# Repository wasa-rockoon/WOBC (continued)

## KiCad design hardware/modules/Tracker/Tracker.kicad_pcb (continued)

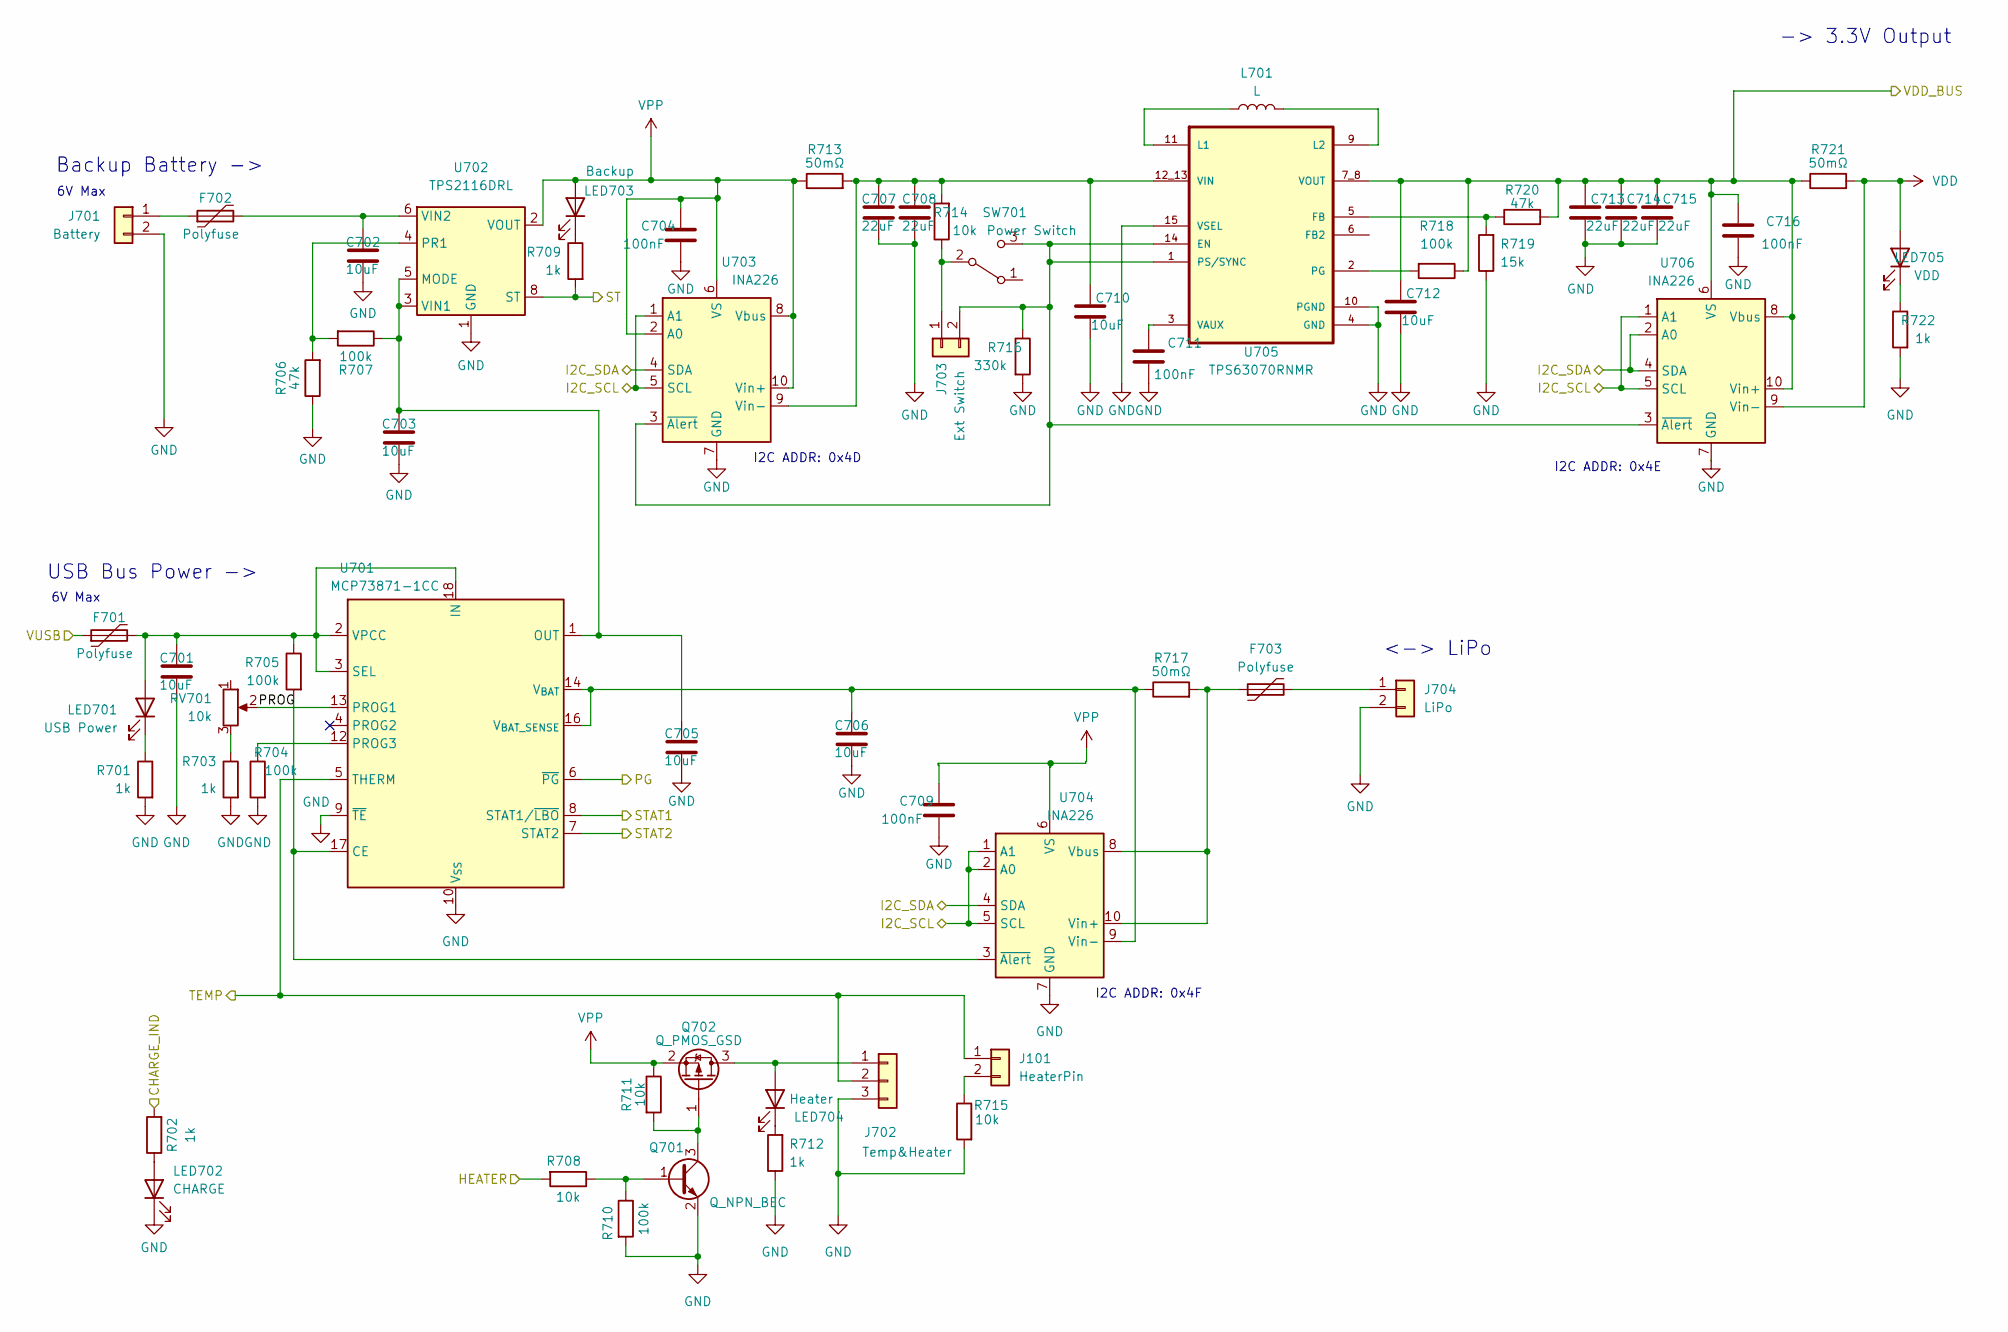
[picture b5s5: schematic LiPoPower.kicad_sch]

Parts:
C701, C702, C703, C705, C706, C710, C712: 10uF; C_0603_1608Metric; LCSC C96446
C704, C709, C711, C716: 100nF; C_0402_1005Metric; LCSC C1525
C707, C708, C713, C714, C715: 22uF; C_0805_2012Metric; LCSC C45783
F701, F702, F703: Polyfuse; Fuse_1206_3216Metric; LCSC C883133
J101: HeaterPin; PinHeader_1x02_P1.27mm_Vertical
J701: Battery; JST_XH_B2B-XH-A_1x02_P2.50mm_Vertical
J702: Temp&Heater; JST_PH_B3B-PH-K_1x03_P2.00mm_Vertical
J703: Ext Switch; JST_PH_B2B-PH-K_1x02_P2.00mm_Vertical
J704: LiPo; JST_PH_B2B-PH-K_1x02_P2.00mm_Vertical
L701: L; L_Wuerth_WE-TPC-3816; LCSC C3033018
LED701: USB Power; LED_0805_2012Metric; LCSC C2297
LED702: CHARGE; LED_0805_2012Metric; LCSC C2296
LED703: Backup; LED_0805_2012Metric; LCSC C2296
LED704: Heater; LED_0805_2012Metric; LCSC C2296
LED705: VDD; LED_0805_2012Metric; LCSC C2297
Q701: Q_NPN_BEC; SOT-23; LCSC C20526
Q702: Q_PMOS_GSD; SOT-23; LCSC C15127
R701, R702, R703, R709, R712, R722: 1k; R_0402_1005Metric; LCSC C11702
R704, R705, R707, R710, R718: 100k; R_0402_1005Metric; LCSC C25741
R706, R720: 47k; R_0402_1005Metric; LCSC C25792
R708, R711, R714, R715: 10k; R_0402_1005Metric; LCSC C25744
R713, R717, R721: 50mΩ; R_0805_2012Metric; LCSC C247602
R716: 330k; R_0402_1005Metric; LCSC C23137
R719: 15k; R_0402_1005Metric; LCSC C25756
RV701: 10k; Potentiometer_Bourns_TC33X_Vertical; LCSC C719176
SW701: Power Switch; SW_Slide_SPDT_Straight_CK_OS102011MS2Q
U701: MCP73871-1CC; QFN-20-1EP_4x4mm_P0.5mm_EP2.5x2.5mm; LCSC C511310
U702: TPS2116DRL; SOT-583-8; LCSC C3235557
U703, U704, U706: INA226; VSSOP-10_3x3mm_P0.5mm; LCSC C49851
U705: TPS63070RNMR; VREG_TPS63070RNMR; LCSC C109322

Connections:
/ESP32/CAN_RX: U701.7 (STAT2); also elsewhere on the board
/ESP32/CAN_TX: U701.8 (STAT1/~LBO); also elsewhere on the board
/ESP32/GPIO6/ADC1_CH5: R709.2, U702.8 (ST); also elsewhere on the board
/ESP32/GPIO7/ADC1_CH6: J101.1, J702.2, U701.5 (THERM); also elsewhere on the board
/ESP32/GPIO8/ADC1_CH7: R702.2; also elsewhere on the board
/ESP32/GPIO9/ADC1_CH8: R708.2; also elsewhere on the board
/ESP32/GPIO10/ADC1_CH9: U701.6 (~PG); also elsewhere on the board
/ESP32/I2C_SCL: U703.1 (A1), U703.5 (SCL), U704.1 (A1), U704.2 (A0), U704.5 (SCL), U706.1 (A1), U706.5 (SCL); also elsewhere on the board
/ESP32/I2C_SDA: U703.4 (SDA), U704.4 (SDA), U706.2 (A0), U706.4 (SDA); also elsewhere on the board
/ESP32/VUSB: F701.1; also elsewhere on the board
/Lipo/PROG: RV701.2, U701.13 (PROG1)
GND: C701.2, C702.2, C703.2, C704.2, C705.2, C706.2, C707.2, C708.2, C709.2, C710.2, C711.2, C712.2, C713.2, C714.2, C715.2, C716.2, J701.2, J702.3, J704.2, LED702.1 (K), Q701.2 (E), R701.2, R703.2, R704.2, R706.1, R710.2, R712.1, R715.2, R716.2, R719.1, R722.2, U701.9 (~TE), U701.10 (V_{SS}), U701.11 (V_{SS}), U701.21 (V_{SS}), U702.1 (GND), U703.7 (GND), U704.7 (GND), U705.4 (GND), U705.10 (PGND), U705.15 (VSEL), U706.7 (GND); also elsewhere on the board
unnamed: J101.2, R715.1
unnamed: F702.1, J701.1
unnamed: J702.1, LED704.2 (A), Q702.3 (D)
unnamed: J703.1, R714.1, SW701.2 (B)
unnamed: J703.2, R716.1, SW701.3 (C), U703.3 (~Alert), U705.1 (PS/SYNC), U705.14 (EN), U706.3 (~Alert)
unnamed: F703.2, J704.1
unnamed: C701.1, F701.2, LED701.2 (A), R705.1, U701.2 (VPCC), U701.3 (SEL), U701.18 (IN), U701.19 (IN)
unnamed: LED701.1 (K), R701.1
unnamed: LED702.2 (A), R702.1
unnamed: LED703.1 (K), R709.1
unnamed: LED704.1 (K), R712.2
unnamed: LED705.1 (K), R722.1
unnamed: Q701.1 (B), R708.1, R710.1
unnamed: Q701.3 (C), Q702.1 (G), R711.2
unnamed: R703.1, RV701.3
unnamed: R705.2, U701.17 (CE), U704.3 (~Alert)
unnamed: R704.1, U701.12 (PROG3)
unnamed: C706.1, R717.1, U701.14 (V_{BAT}), U701.15 (V_{BAT}), U701.16 (V_{BAT_SENSE}), U704.9 (Vin-)
unnamed: C703.1, C705.1, R707.1, U701.1 (OUT), U701.20 (OUT), U702.3 (VIN1), U702.5 (MODE)
unnamed: R706.2, R707.2, U702.4 (PR1)
unnamed: C702.1, F702.2, U702.6 (VIN2)
unnamed: C707.1, C708.1, C710.1, R713.2, R714.2, U703.9 (Vin-), U705.12_13 (VIN)
unnamed: F703.1, R717.2, U704.8 (Vbus), U704.10 (Vin+)
unnamed: R719.2, R720.1, U705.5 (FB)
unnamed: L701.1, U705.11 (L1)
unnamed: L701.2, U705.9 (L2)
unnamed: R718.2, U705.2 (PG)
unnamed: C711.1, U705.3 (VAUX)
VDD: C712.1, C713.1, C714.1, C715.1, C716.1, LED705.2 (A), R718.1, R720.2, R721.1, R721.2, U705.7_8 (VOUT), U706.6 (VS), U706.8 (Vbus), U706.9 (Vin-), U706.10 (Vin+); also elsewhere on the board
VPP: C704.1, C709.1, LED703.2 (A), Q702.2 (S), R711.1, R713.1, U702.2 (VOUT), U702.7 (VOUT), U703.2 (A0), U703.6 (VS), U703.8 (Vbus), U703.10 (Vin+), U704.6 (VS)

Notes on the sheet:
6V Max
USB Bus Power ->
<-> LiPo
I2C ADDR: 0x4D
I2C ADDR: 0x4F
-> 3.3V Output
I2C ADDR: 0x4E
Backup Battery ->

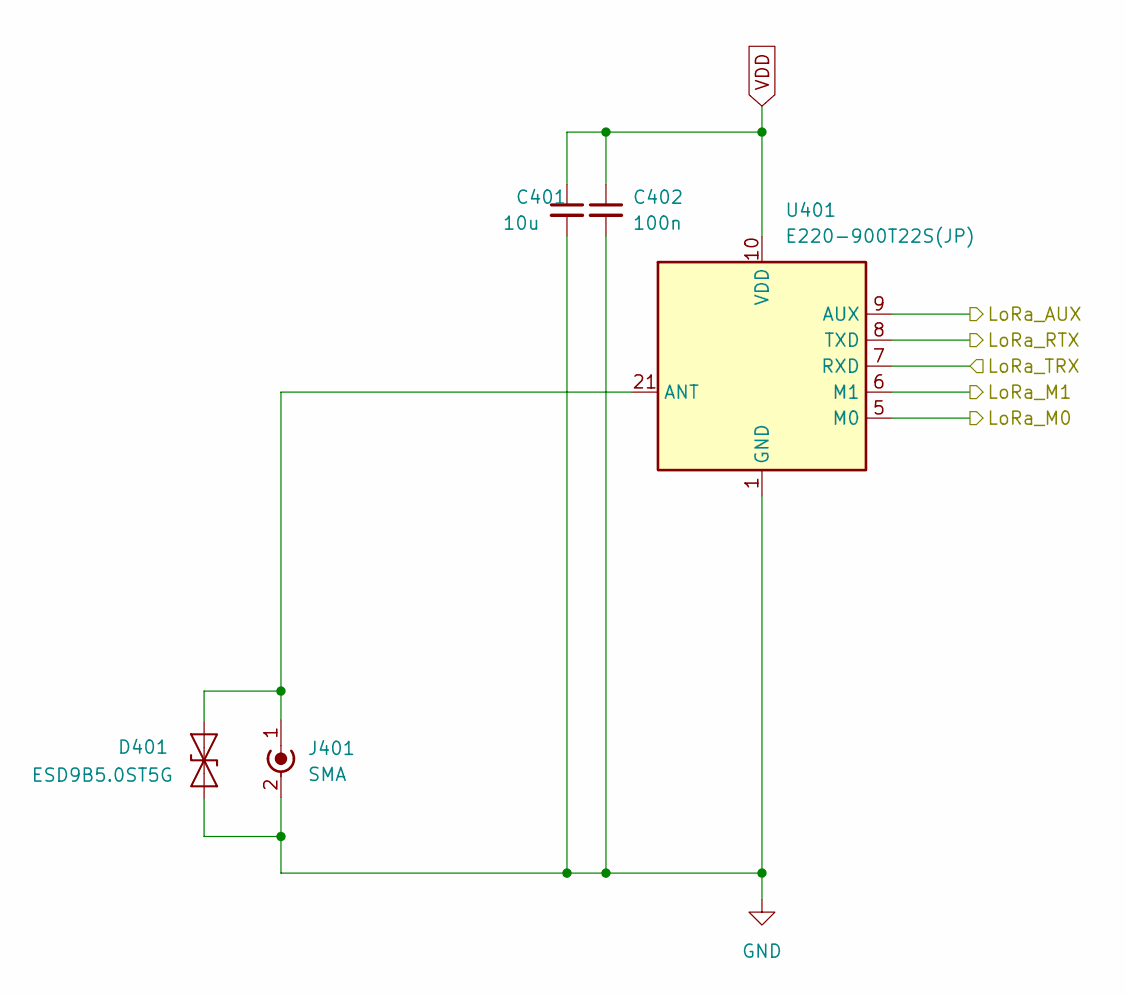
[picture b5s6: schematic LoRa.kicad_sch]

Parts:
C401: 10u; C_0603_1608Metric; LCSC C96446
C402: 100n; C_0402_1005Metric; LCSC C1525
D401: ESD9B5.0ST5G; D_SOD-882D; LCSC C7420372
J401: SMA; SMA_Amphenol_132203-12_Horizontal; LCSC C2693813
U401: E220-900T22S(JP)

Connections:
/ESP32/GPIO11: U401.6 (M1); also elsewhere on the board
/ESP32/GPIO12: U401.5 (M0); also elsewhere on the board
/ESP32/GPIO38: U401.7 (RXD); also elsewhere on the board
/ESP32/GPIO39: U401.8 (TXD); also elsewhere on the board
/ESP32/GPIO40: U401.9 (AUX); also elsewhere on the board
GND: C401.2, C402.2, D401.1 (A1), J401.2 (Ext), U401.1 (GND), U401.2 (GND), U401.3 (GND), U401.4 (GND), U401.11 (GND), U401.13 (GND), U401.19 (GND), U401.20 (GND), U401.22 (GND); also elsewhere on the board
unnamed: D401.2 (A2), J401.1 (In), U401.21 (ANT)
VDD: C401.1, C402.1, U401.10 (VDD); also elsewhere on the board

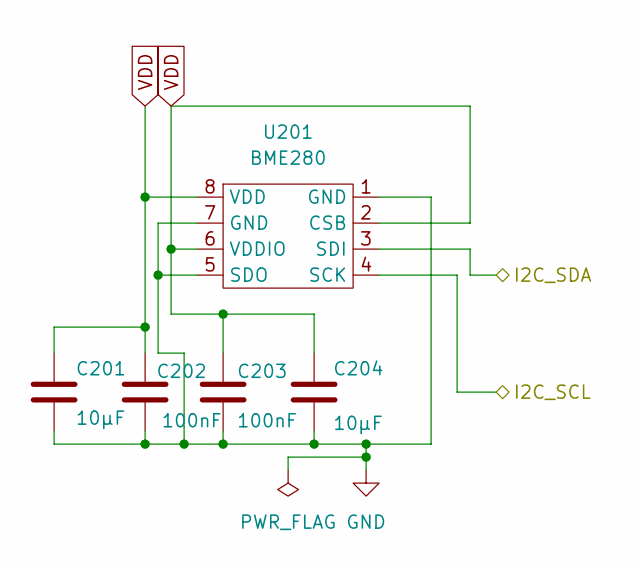
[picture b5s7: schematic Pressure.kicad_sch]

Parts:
C201, C204: 10μF; C_0603_1608Metric; LCSC C96446
C202, C203: 100nF; C_0402_1005Metric; LCSC C1525
U201: BME280; LCSC C92489

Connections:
/ESP32/I2C_SCL: U201.4 (SCK); also elsewhere on the board
/ESP32/I2C_SDA: U201.3 (SDI); also elsewhere on the board
GND: C201.2, C202.2, C203.2, C204.2, U201.1 (GND), U201.5 (SDO), U201.7 (GND); also elsewhere on the board
VDD: C201.1, C202.1, C203.1, C204.1, U201.2 (CSB), U201.6 (VDDIO), U201.8 (VDD); also elsewhere on the board

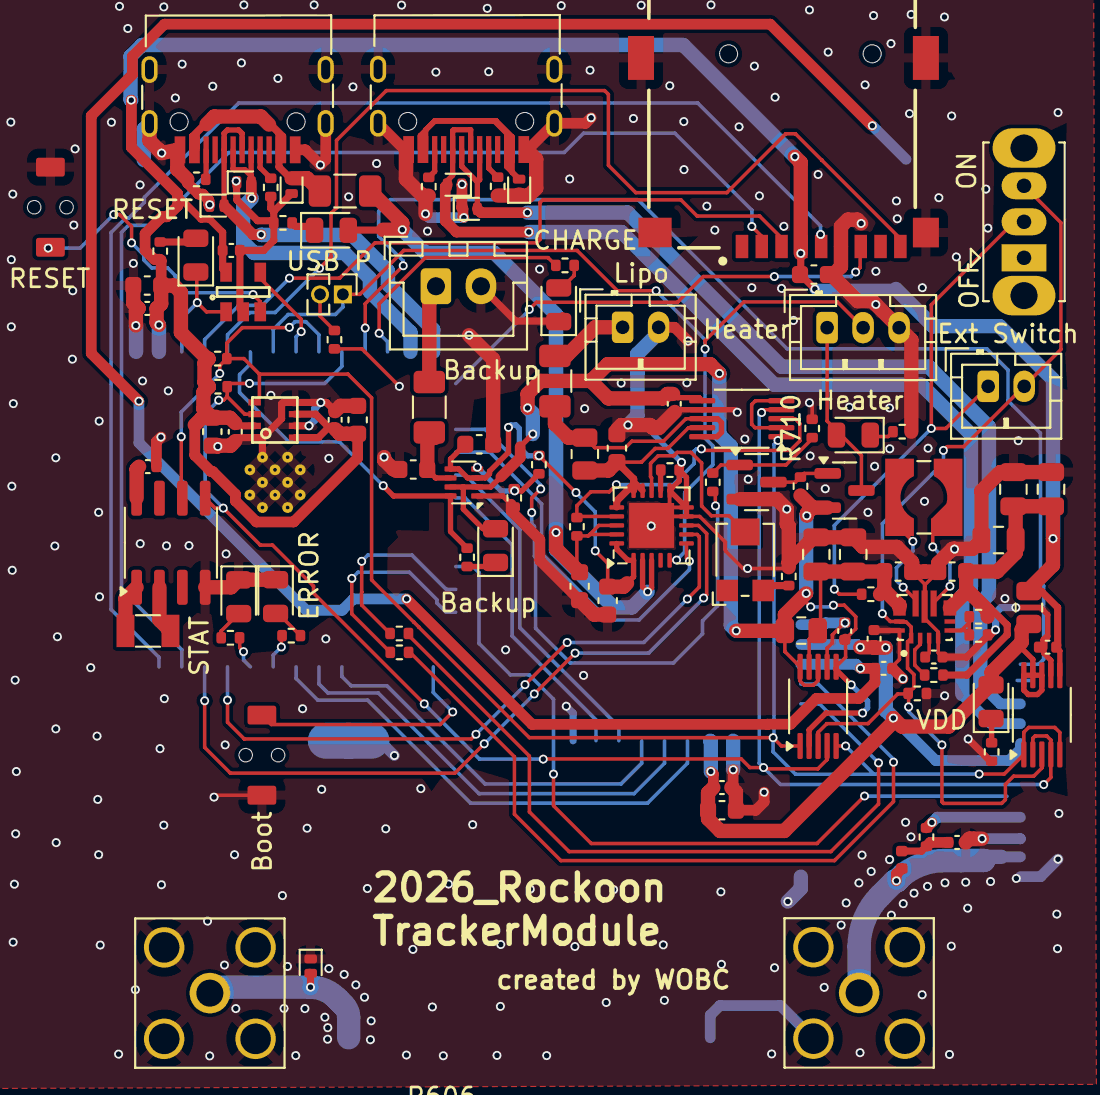
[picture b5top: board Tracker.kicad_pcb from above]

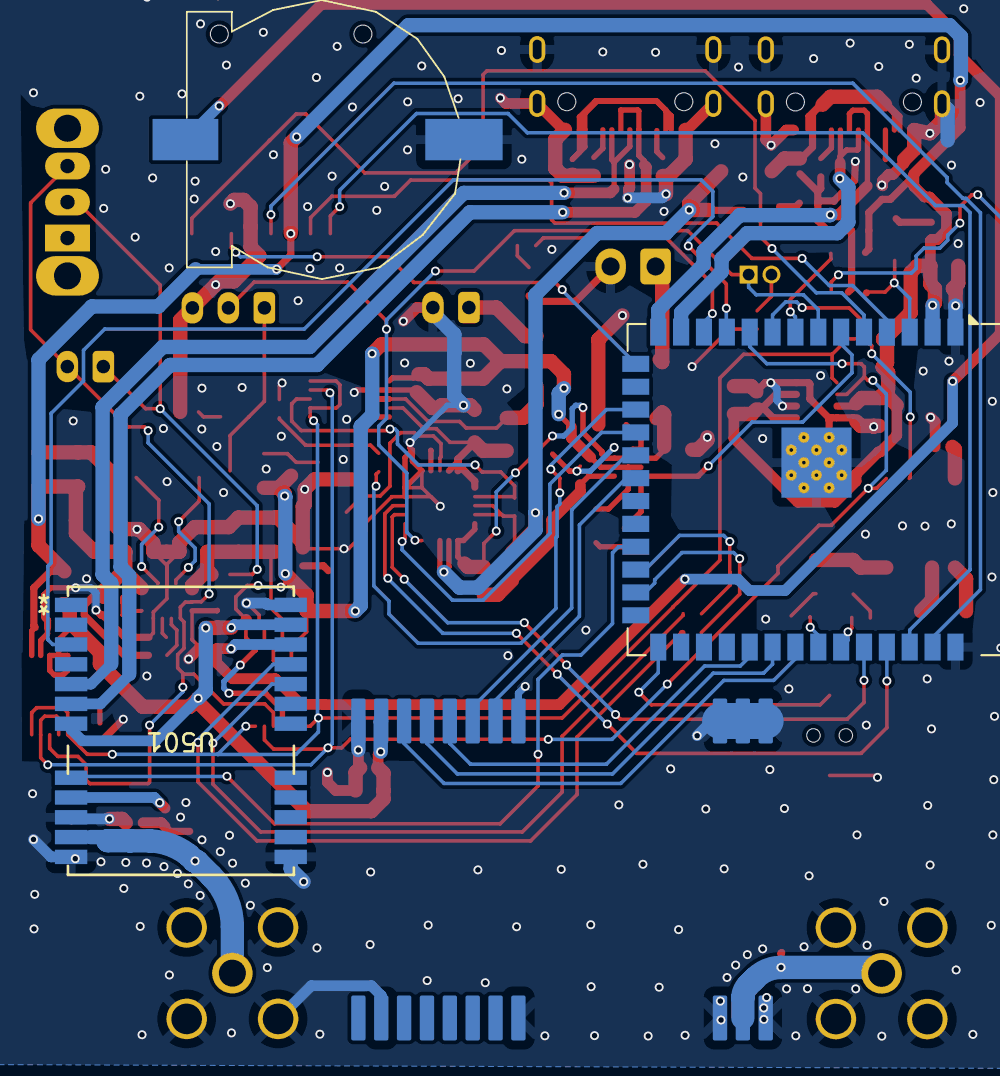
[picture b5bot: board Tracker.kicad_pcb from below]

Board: 2 copper layers, 114 parts (4 on the bottom side), 84 nets.

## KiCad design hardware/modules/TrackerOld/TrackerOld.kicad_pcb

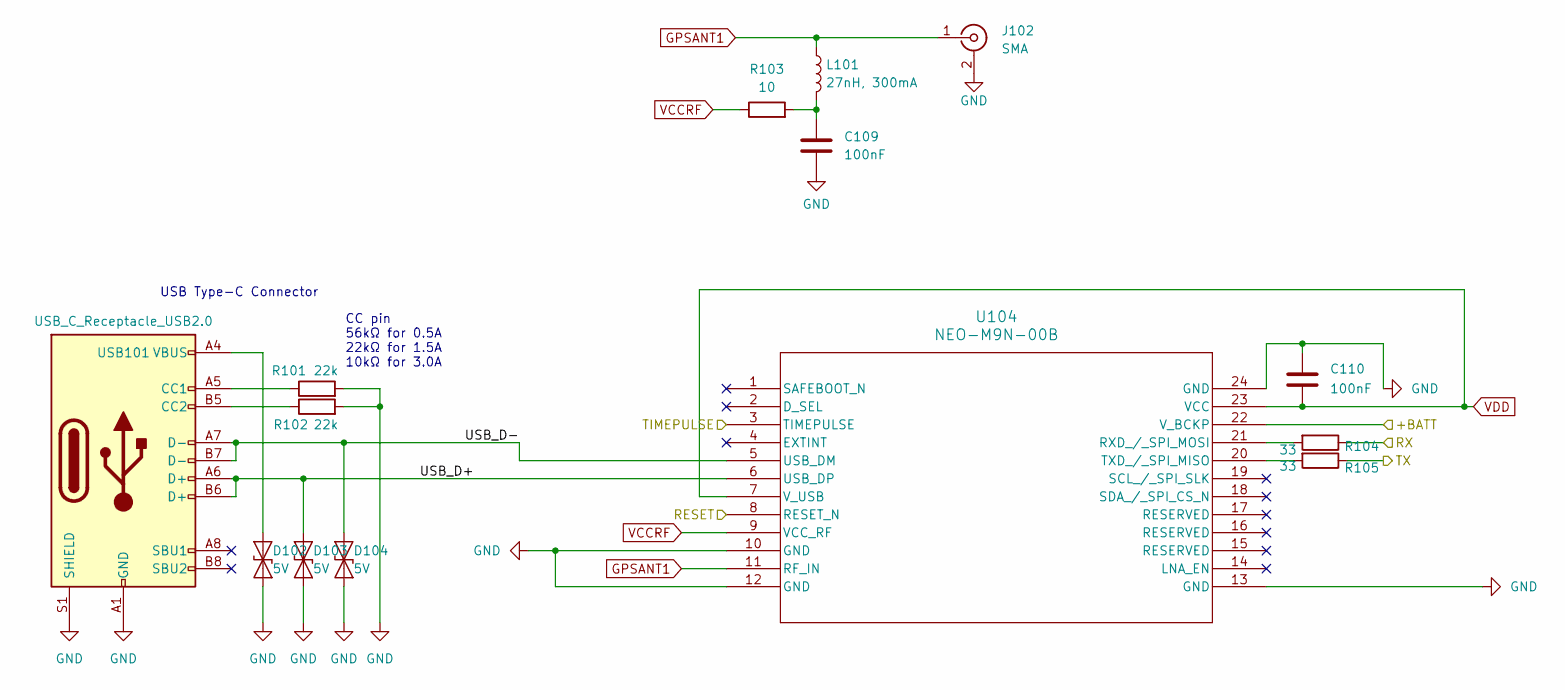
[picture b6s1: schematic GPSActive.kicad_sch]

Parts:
C109, C110: 100nF; C_0402_1005Metric; LCSC C1525
D102, D103, D104: 5V; D_SOD-882D; LCSC C7420372
J102: SMA; SMA_Amphenol_132203-12_Horizontal; LCSC C2693813
L101: 27nH, 300mA; L_0402_1005Metric
R101, R102: 22k; R_0402_1005Metric; LCSC C25768
R103: 10; R_0402_1005Metric; LCSC C25139
R104, R105: 33; R_0402_1005Metric; LCSC C25105
U104: NEO-M9N-00B; SMT_9N-00B_UBL
USB101: USB_C_Receptacle_USB2.0; USB_C_TYPEC-301S-ACP16X7; LCSC C2982481

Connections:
/ESP32/GPIO18: U104.3 (TIMEPULSE); also elsewhere on the board
/ESP32/GPIO21: U104.8 (RESET_N); also elsewhere on the board
/ESP32/GPIO47: R105.1; also elsewhere on the board
/ESP32/GPIO48: R104.1; also elsewhere on the board
/GPSActive/+BATT: U104.22 (V_BCKP)
/GPSActive/USB_D+: D103.2 (A2), U104.6 (USB_DP), USB101.A6 (D+), USB101.B6 (D+)
/GPSActive/USB_D-: D104.2 (A2), U104.5 (USB_DM), USB101.A7 (D-), USB101.B7 (D-)
GND: C109.2, C110.1, D102.1 (A1), D103.1 (A1), D104.1 (A1), J102.2 (Ext), R101.2, R102.2, U104.10 (GND), U104.12 (GND), U104.13 (GND), U104.24 (GND), USB101.A1 (GND), USB101.A12 (GND), USB101.B1 (GND), USB101.B12 (GND), USB101.S1 (SHIELD); also elsewhere on the board
GPSANT1: J102.1 (In), L101.1, U104.11 (RF_IN)
unnamed: C109.1, L101.2, R103.2
unnamed: D102.2 (A2), USB101.A4 (VBUS), USB101.A9 (VBUS), USB101.B4 (VBUS), USB101.B9 (VBUS)
unnamed: R104.2, U104.21 (RXD_/_SPI_MOSI)
unnamed: R105.2, U104.20 (TXD_/_SPI_MISO)
unnamed: R101.1, USB101.A5 (CC1)
unnamed: R102.1, USB101.B5 (CC2)
VCCRF: R103.1, U104.9 (VCC_RF)
VDD: C110.2, U104.7 (V_USB), U104.23 (VCC); also elsewhere on the board

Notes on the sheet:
CC pin 56kΩ for 0.5A 22kΩ for 1.5A 10kΩ for 3.0A
USB Type-C Connector

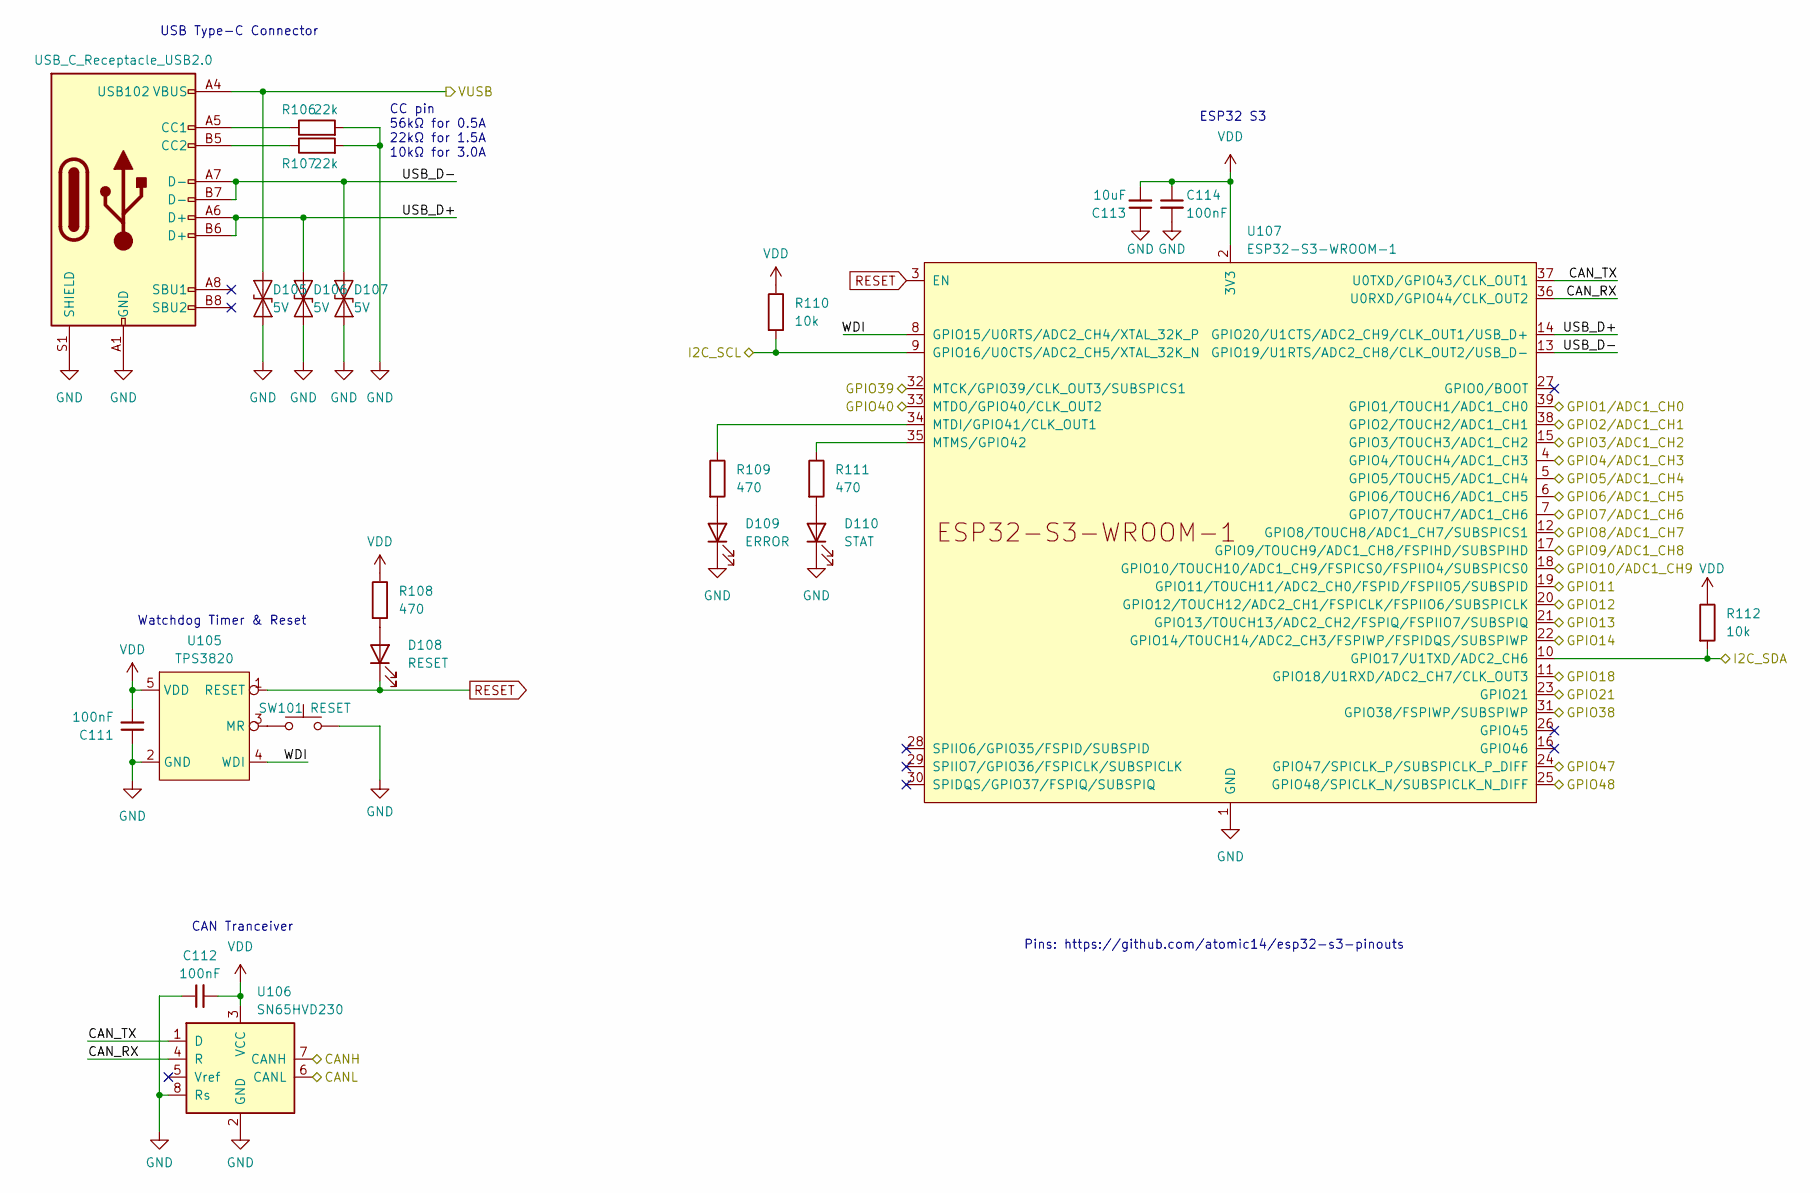
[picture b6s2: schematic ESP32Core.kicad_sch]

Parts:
C111, C112, C114: 100nF; C_0402_1005Metric; LCSC C1525
C113: 10uF; C_0603_1608Metric; LCSC C96446
D105, D106, D107: 5V; D_SOD-923; LCSC C7420372
D108: RESET; LED_0603_1608Metric; LCSC C2296
D109: ERROR; LED_0603_1608Metric; LCSC C84256
D110: STAT; LED_0603_1608Metric; LCSC C2297
R106, R107: 22k; R_0402_1005Metric; LCSC C25768
R108, R109, R111: 470; R_0402_1005Metric; LCSC C25117
R110, R112: 10k; R_0402_1005Metric; LCSC C25744
SW101: RESET; TVAF06-A020B-R
U105: TPS3820; SOT_23_5; LCSC C130064
U106: SN65HVD230; SOIC-8_3.9x4.9mm_P1.27mm; LCSC C12084
U107: ESP32-S3-WROOM-1
USB102: USB_C_Receptacle_USB2.0; USB_C_TYPEC-301S-ACP16X7; LCSC C2982481

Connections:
/ESP32/CANH: U106.7 (CANH); also elsewhere on the board
/ESP32/CANL: U106.6 (CANL); also elsewhere on the board
/ESP32/CAN_RX: U106.4 (R), U107.36 (U0RXD/GPIO44/CLK_OUT2)
/ESP32/CAN_TX: U106.1 (D), U107.37 (U0TXD/GPIO43/CLK_OUT1)
/ESP32/GPIO1/ADC1_CH0: U107.39 (GPIO1/TOUCH1/ADC1_CH0); also elsewhere on the board
/ESP32/GPIO2/ADC1_CH1: U107.38 (GPIO2/TOUCH2/ADC1_CH1); also elsewhere on the board
/ESP32/GPIO3/ADC1_CH2: U107.15 (GPIO3/TOUCH3/ADC1_CH2); also elsewhere on the board
/ESP32/GPIO4/ADC1_CH3: U107.4 (GPIO4/TOUCH4/ADC1_CH3); also elsewhere on the board
/ESP32/GPIO5/ADC1_CH4: U107.5 (GPIO5/TOUCH5/ADC1_CH4); also elsewhere on the board
/ESP32/GPIO6/ADC1_CH5: U107.6 (GPIO6/TOUCH6/ADC1_CH5); also elsewhere on the board
/ESP32/GPIO7/ADC1_CH6: U107.7 (GPIO7/TOUCH7/ADC1_CH6); also elsewhere on the board
/ESP32/GPIO8/ADC1_CH7: U107.12 (GPIO8/TOUCH8/ADC1_CH7/SUBSPICS1); also elsewhere on the board
/ESP32/GPIO9/ADC1_CH8: U107.17 (GPIO9/TOUCH9/ADC1_CH8/FSPIHD/SUBSPIHD); also elsewhere on the board
/ESP32/GPIO10/ADC1_CH9: U107.18 (GPIO10/TOUCH10/ADC1_CH9/FSPICS0/FSPIIO4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); also elsewhere on the board
/ESP32/GPIO11: U107.19 (GPIO11/TOUCH11/ADC2_CH0/FSPID/FSPIIO5/S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); also elsewhere on the board
/ESP32/GPIO12: U107.20 (GPIO12/TOUCH12/ADC2_CH1/FSPICLK/FSPIIO6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); also elsewhere on the board
/ESP32/GPIO13: U107.21 (GPIO13/TOUCH13/ADC2_CH2/FSPIQ/FSPIIO7/S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); also elsewhere on the board
/ESP32/GPIO14: U107.22 (GPIO14/TOUCH14/ADC2_CH3/FSPIWP/FSPIDQS/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); also elsewhere on the board
/ESP32/GPIO18: U107.11 (GPIO18/U1RXD/ADC2_CH7/CLK_OUT3); also elsewhere on the board
/ESP32/GPIO21: U107.23 (GPIO21); also elsewhere on the board
/ESP32/GPIO38: U107.31 (GPIO38/FSPIWP/SUBSPIWP); also elsewhere on the board
/ESP32/GPIO39: U107.32 (MTCK/GPIO39/CLK_OUT3/SUBSPICS1); also elsewhere on the board
/ESP32/GPIO40: U107.33 (MTDO/GPIO40/CLK_OUT2); also elsewhere on the board
/ESP32/GPIO47: U107.24 (GPIO47/SPICLK_P/SUBSPICLK_P_DIFF); also elsewhere on the board
/ESP32/GPIO48: U107.25 (GPIO48/SPICLK_N/SUBSPICLK_N_DIFF); also elsewhere on the board
/ESP32/I2C_SCL: R110.2, U107.9 (GPIO16/U0CTS/ADC2_CH5/XTAL_32K_N); also elsewhere on the board
/ESP32/I2C_SDA: R112.2, U107.10 (GPIO17/U1TXD/ADC2_CH6); also elsewhere on the board
/ESP32/USB_D+: D106.2 (A2), U107.14 (GPIO20/U1CTS/ADC2_CH9/CLK_OUT1/USB_D+), USB102.A6 (D+), USB102.B6 (D+)
/ESP32/USB_D-: D107.2 (A2), U107.13 (GPIO19/U1RTS/ADC2_CH8/CLK_OUT2/USB_D-), USB102.A7 (D-), USB102.B7 (D-)
/ESP32/VUSB: D105.2 (A2), USB102.A4 (VBUS), USB102.A9 (VBUS), USB102.B4 (VBUS), USB102.B9 (VBUS)
/ESP32/WDI: U105.4 (WDI), U107.8 (GPIO15/U0RTS/ADC2_CH4/XTAL_32K_P)
GND: C111.1, C112.1, C113.1, C114.2, D105.1 (A1), D106.1 (A1), D107.1 (A1), D109.1 (K), D110.1 (K), R106.2, R107.2, SW101.2, U105.2 (GND), U106.2 (GND), U106.8 (Rs), U107.1 (GND), U107.40 (GND), U107.41 (GND), USB102.A1 (GND), USB102.A12 (GND), USB102.B1 (GND), USB102.B12 (GND), USB102.S1 (SHIELD); also elsewhere on the board
unnamed: D108.2 (A), R108.2
unnamed: D109.2 (A), R109.2
unnamed: D110.2 (A), R111.2
unnamed: SW101.1, U105.3 (MR)
unnamed: R109.1, U107.34 (MTDI/GPIO41/CLK_OUT1)
unnamed: R111.1, U107.35 (MTMS/GPIO42)
unnamed: R106.1, USB102.A5 (CC1)
unnamed: R107.1, USB102.B5 (CC2)
RESET: D108.1 (K), U105.1 (RESET), U107.3 (EN)
VDD: C111.2, C112.2, C113.2, C114.1, R108.1, R110.1, R112.1, U105.5 (VDD), U106.3 (VCC), U107.2 (3V3); also elsewhere on the board

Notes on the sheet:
ESP32 S3
Watchdog Timer & Reset
CAN Tranceiver
Pins: https://github.com/atomic14/esp32-s3-pinouts
USB Type-C Connector
CC pin 56kΩ for 0.5A 22kΩ for 1.5A 10kΩ for 3.0A

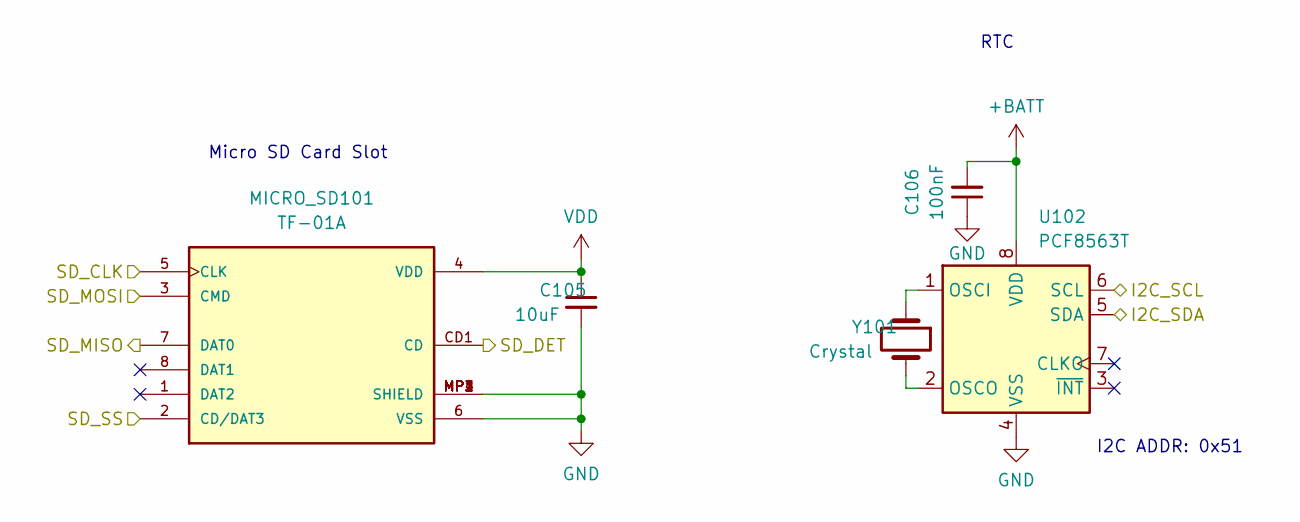
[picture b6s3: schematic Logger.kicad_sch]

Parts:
C105: 10uF; C_0402_1005Metric; LCSC C96446
C106: 100nF; C_0402_1005Metric; LCSC C1525
MICRO_SD101: TF-01A; LCSC C5155563
U102: PCF8563T; SOIC-8_3.9x4.9mm_P1.27mm; LCSC C5795601
Y101: Crystal; Crystal_SMD_3215-2Pin_3.2x1.5mm; LCSC C9002

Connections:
+BATT: C106.2, U102.8 (VDD)
/ESP32/GPIO1/ADC1_CH0: MICRO_SD101.5 (CLK); also elsewhere on the board
/ESP32/GPIO2/ADC1_CH1: MICRO_SD101.2 (CD/DAT3); also elsewhere on the board
/ESP32/GPIO3/ADC1_CH2: MICRO_SD101.7 (DAT0); also elsewhere on the board
/ESP32/GPIO4/ADC1_CH3: MICRO_SD101.3 (CMD); also elsewhere on the board
/ESP32/GPIO5/ADC1_CH4: MICRO_SD101.CD1 (CD); also elsewhere on the board
/ESP32/I2C_SCL: U102.6 (SCL); also elsewhere on the board
/ESP32/I2C_SDA: U102.5 (SDA); also elsewhere on the board
GND: C105.2, C106.1, MICRO_SD101.6 (VSS), MICRO_SD101.MP1 (SHIELD), MICRO_SD101.MP2 (SHIELD), MICRO_SD101.MP3 (SHIELD), MICRO_SD101.MP4 (SHIELD), U102.4 (VSS); also elsewhere on the board
unnamed: U102.1 (OSCI), Y101.1
unnamed: U102.2 (OSCO), Y101.2
VDD: C105.1, MICRO_SD101.4 (VDD); also elsewhere on the board

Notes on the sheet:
Micro SD Card Slot
RTC
I2C ADDR: 0x51
